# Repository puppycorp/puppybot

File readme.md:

# PuppyBot

PuppyBot's controller, Linux runtime, simulator, visual-control training and
classic ESP32 serial firmware are implemented in Flexscript. The maintained
source is in [`src/`](src/README.md), organized by purpose.

## Run

From the repository root:

```sh
flexscript run puppybot.flex
```

Open **http://127.0.0.1:8081/** for the robot dashboard. The default is a fake
servo bus. The launcher compiles and executes the native runtime; configuration
comes from [`puppybot.json`](puppybot.json). See the
[controller instructions](src/README.md) for physical serial control and output enable.

Run a separate 3D simulator with `flexscript run simulator.flex`. It prints the
private serial device and the controller connection command. For the lightweight
servo model use `flexscript run simulator.flex --servo-only`.

For autonomous simulation and visual-control experiments:

```sh
flexscript run sim.flex --list-cases
flexscript run sim.flex --case house-blocks-into-box --drift 10
./src/control.sh build
```

See [simulation](src/sim/README.md), [visual control](src/control/README.md),
[Gym](src/gym/README.md) and [exploration](src/exploration/README.md).
Python remains in experiment orchestration, data preparation and independent
verification; the repository is not exclusively Flexscript.

## Build and verify

Install Flexscript and keep the sibling `../flexscript` Git checkout available.
The native build snapshots a pinned compiler/library revision from that checkout
into `build/native-toolchain`; it never changes the sibling checkout. Set
`FLEXSCRIPT_SOURCE` to use another checkout containing that revision. To supply
an already verified matching toolchain instead, set `FLEXSCRIPT_COMPILER` and
`FLEXSCRIPT_ROOT` (and `FLEXSCRIPT_SOURCE` for firmware link tooling).

```sh
./src/scripts/build-runtime.sh
./src/scripts/test-runtime.sh
```

These commands build and test the native controller, HTTP/WebSocket runtime,
CLI, serial simulator and simulated firmware without the GPU training toolchain.
The tests use loopback sockets and private PTYs, not a physical robot.

The broader `./src/scripts/build.sh` and `./src/scripts/test.sh` include Gym,
vision, controller differential tests and additional tooling. They require a
compatible Flexscript source checkout and GPU libraries; set `FLEXSCRIPT_ROOT`
and follow [the detailed build instructions](src/README.md).

For classic ESP32 serial firmware:

```sh
python3 src/scripts/prepare-esp32-tools.py
./src/scripts/build-esp32.sh
```

See [firmware wiring, verification and flashing](src/firmware/README.md).
The Flexscript target is serial-only: Wi-Fi/WebSocket/mDNS, Android wireless
control, persistent calibration and physical hardware qualification are still
separate work. Replacing the source layout does not establish those capabilities.

## Repository layout

| Path | Purpose |
| --- | --- |
| `src/core/`, `src/transport/` | Shared controller, kinematics, safety and protocol |
| `src/runtime/`, `src/host/`, `src/cli/` | Linux service, dashboard, serial adapter and CLI |
| `src/firmware/`, `src/platform/` | ESP32 and simulated firmware adapters |
| `src/sim/`, `src/simulator/`, `src/gym/` | 3D simulation, serial plant and rollout UI |
| `src/control/`, `src/ml/`, `src/vision/`, `src/exploration/` | Learning, inference and navigation |
| `src/scripts/`, `src/tests/` | Build tools and verification |
| `tests/reference/rust-core/` | Original Rust controller used only as a test oracle |
| `datasets/`, `experiments/`, `diary/` | Dataset recipes, experiment programs and research notes |
| `build/flex/sim/` | Local generated datasets and experiment artifacts |
| `models/`, `robotdreams/` | Owned assets and retained historical scene/calibration evidence |
| `android/`, `python/`, `design/` | Android client, servo service utilities and electronics |

The Rust runtime, CLI, ESP32 firmware and collision tools are retired from the
maintained source tree; earlier versions remain in Git history. The native
build workflow packages Flexscript runtime binaries and the Flexscript ESP32
ROM image. The Android client remains a separate application.

`flex` is a compatibility symlink to `src`; `puppybot/core` points to the Rust
test reference. New development uses the canonical paths. Existing experiments,
receipts and `build/flex` output paths are not renamed by this migration.
Source changes still require fresh provenance checks before an old run can be
repeated; a compatibility path does not guarantee identical source hashes.

## Dataset storage

Actual data lives primarily under `build/flex/sim/`; `datasets/` contains recipes
and documentation. Follow [the storage rules](AGENTS.md#experiment-storage):
budget every run, preserve required evidence, review retention when it finishes,
and verify physical space recovered after cleanup. Git-ignored data is not
necessarily disposable.

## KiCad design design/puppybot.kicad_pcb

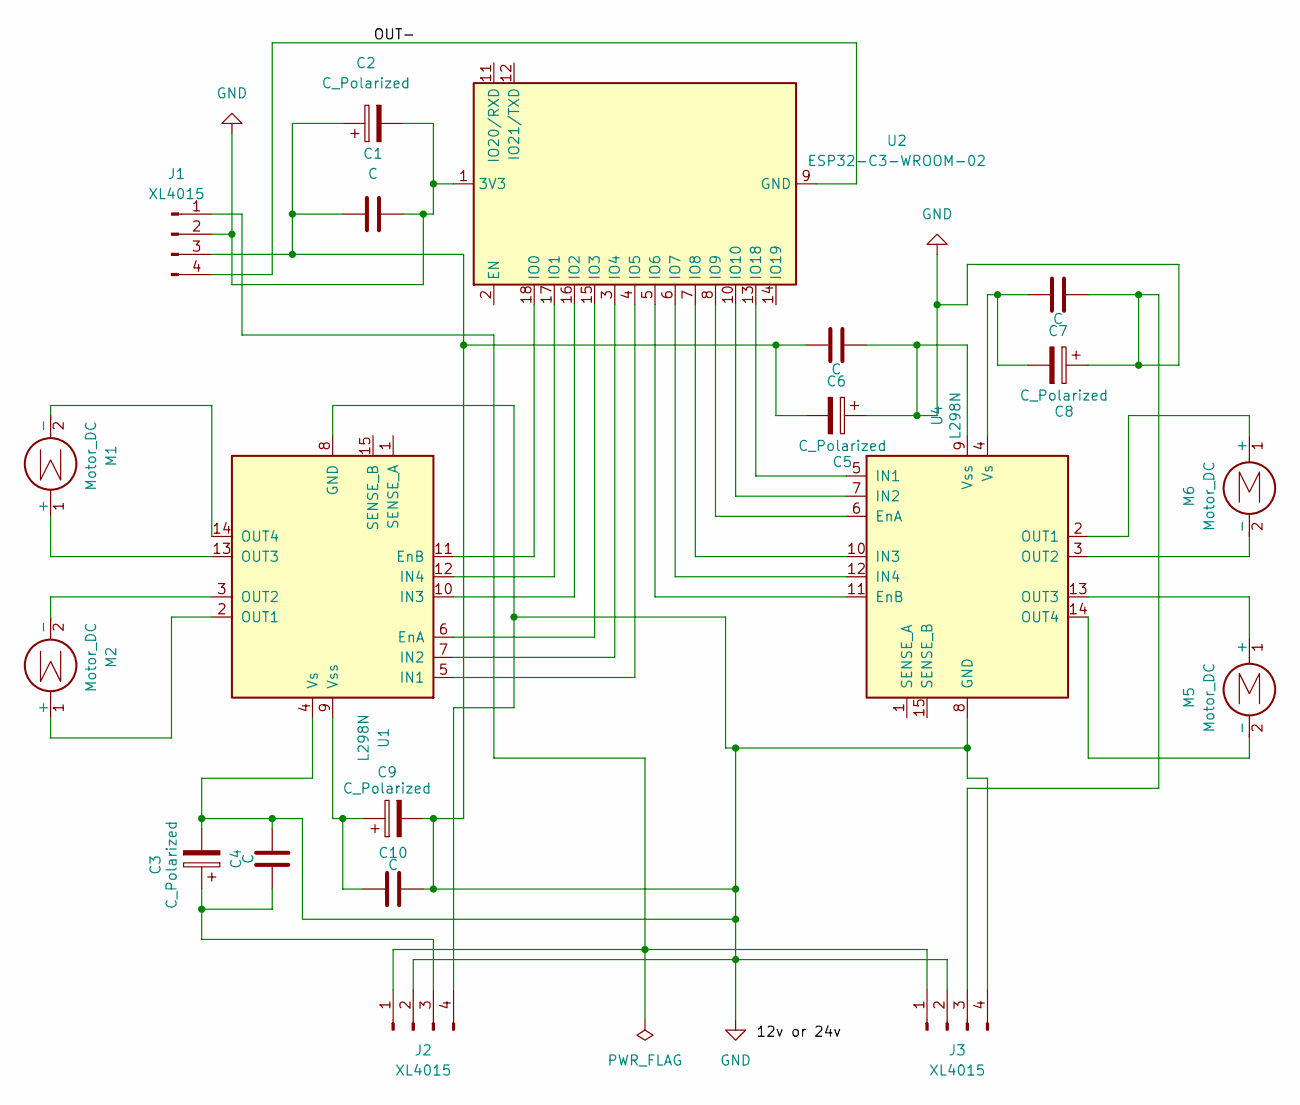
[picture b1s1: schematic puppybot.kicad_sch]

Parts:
C1, C4, C6, C7, C10: C; C_0805_2012Metric
C2, C3, C5, C8, C9: C_Polarized; CP_Radial_D5.0mm_P2.00mm
J1, J2, J3: XL4015; FanPinHeader_1x04_P2.54mm_Vertical
M1, M2, M5, M6: Motor_DC; TerminalBlock_RND_205-00234_1x04_P5.08mm_Horizontal
U1, U4: L298N; DIP-16_W7.62mm
U2: ESP32-C3-WROOM-02

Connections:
/OUT-: J1.4, U2.9 (GND), U2.19 (GND)
GND: C1.1, C1.2, C2.1, C2.2, C3.2, C4.2, C5.1, C5.2, C6.1, C6.2, C7.1, C8.1, C9.2, C10.2, J1.2, J1.3, J2.2, J2.4, J3.2, J3.3, J3.4, U1.4 (Vs), U1.8 (GND), U2.1 (3V3), U4.8 (GND), U4.9 (Vss)
unnamed: J1.1, J2.1, J3.1
unnamed: C3.1, C4.1, J2.3
unnamed: M1.1 (+), U1.13 (OUT3)
unnamed: M1.2 (-), U1.14 (OUT4)
unnamed: M2.1 (+), U1.2 (OUT1)
unnamed: M2.2 (-), U1.3 (OUT2)
unnamed: M5.1 (+), U4.13 (OUT3)
unnamed: M5.2 (-), U4.14 (OUT4)
unnamed: M6.1 (+), U4.2 (OUT1)
unnamed: M6.2 (-), U4.3 (OUT2)
unnamed: U1.6 (EnA), U2.15 (IO3)
unnamed: U1.11 (EnB), U2.18 (IO0)
unnamed: U1.5 (IN1), U2.4 (IO5)
unnamed: U1.7 (IN2), U2.3 (IO4)
unnamed: U1.10 (IN3), U2.16 (IO2)
unnamed: U1.12 (IN4), U2.17 (IO1)
unnamed: C9.1, C10.1, U1.9 (Vss)
unnamed: U2.5 (IO6), U4.11 (EnB)
unnamed: U2.6 (IO7), U4.12 (IN4)
unnamed: U2.7 (IO8), U4.10 (IN3)
unnamed: U2.8 (IO9), U4.6 (EnA)
unnamed: U2.10 (IO10), U4.7 (IN2)
unnamed: U2.13 (IO18), U4.5 (IN1)
unnamed: C7.2, C8.2, U4.4 (Vs)

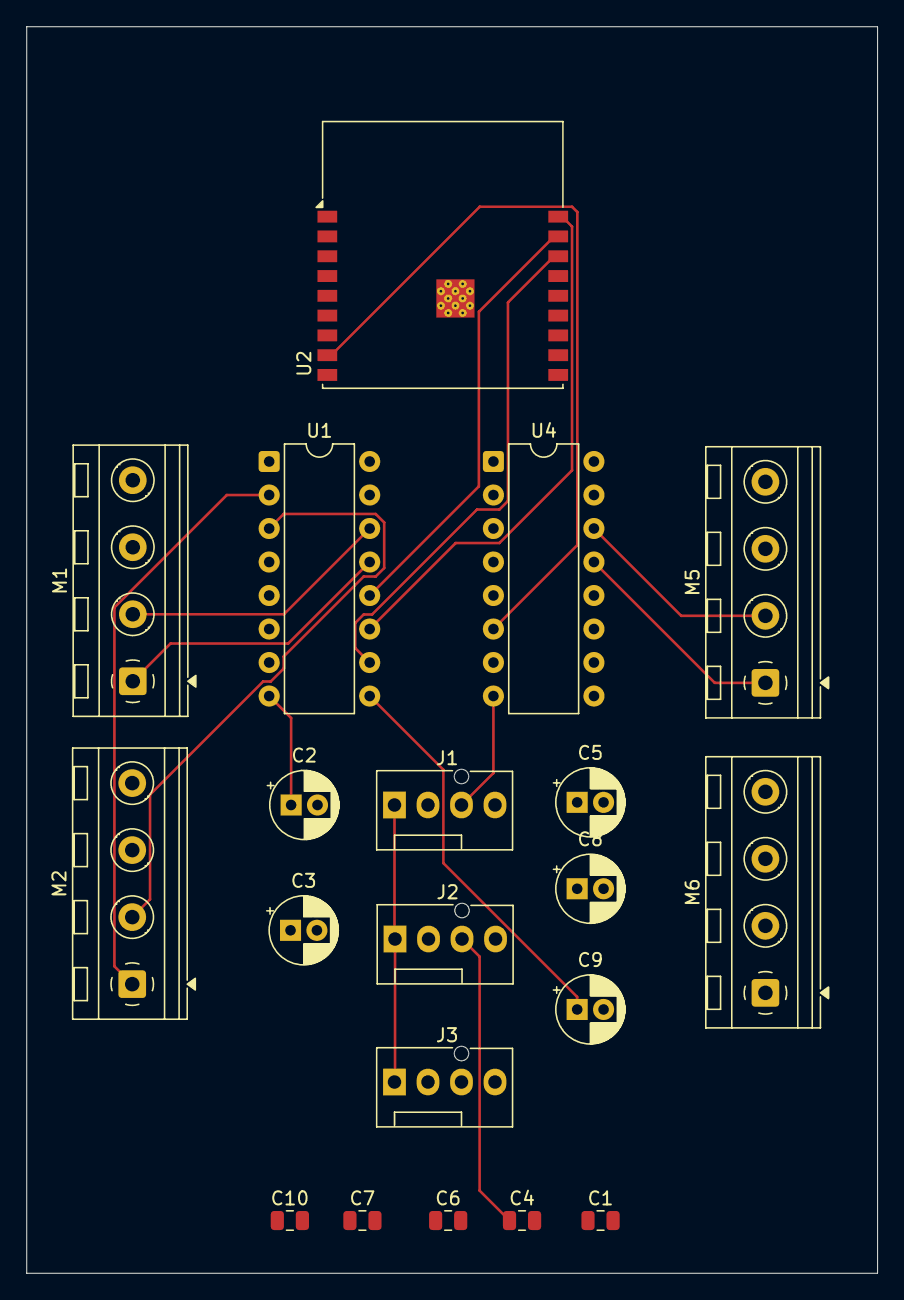
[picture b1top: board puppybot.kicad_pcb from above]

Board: 2 copper layers, 64.5 x 94.5 mm, 20 parts (0 on the bottom side), 26 nets.

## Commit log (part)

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2025-03-09 this is the way
2025-03-09 things
2025-03-22 update elecric design
2025-03-31 new things
2025-04-01 add things
2025-04-02 making structure
2025-04-07 add readme
2025-04-07 save
2025-04-07 start protocol impl
2025-04-09 code
2025-04-12 ping pong with esp works
2025-04-12 moving files and drive
2025-04-12 wow driving forward works
2025-04-13 improve controls now can move forward and backwards
2025-04-13 implement safety stopping of motors if command is not repeated
2025-04-17 trying to make bluetooth to work
2025-04-17 changes to motor control
2025-04-17 add esp32 build
2025-04-17 remove one readme
2025-04-17 dont upload firmware yet
2025-04-17 modify pipeline
2025-04-17 make SERVER_HOST optional
2025-04-17 run gitlab ci always
2025-04-17 change working directory
2025-04-17 add cache to esp32 build
2025-04-17 now the build should work
2025-05-20 Add Android app skeleton
2025-06-11 design change
2025-06-12 run clang format
2025-06-12 some agent things
2025-06-14 Document servo steering
2025-06-14 clang format all c and h files
2025-06-14 format
2025-06-14 run prettier format
2025-06-14 add npm run format to format script
2025-06-14 disable esp build from pipeline fro now
2025-06-14 it works
2025-06-14 add prepare-agent.sh
2025-06-15 Add servo steering control (#2)
2025-06-15 formating
2025-07-06 puppybot v0.6
2025-09-14 it works i guess
2025-09-14 initialize android app
2025-10-05 implement controlling the bot with android app
2025-10-05 Add joystick control mode to Android app
2025-10-05 fix not working with new espidf also add speed parsing
2025-10-05 fix build issues
2025-10-05 Add joystick control mode to Android app (#3)
2025-10-05 improve joystick controls
2025-10-06 adding bluetooth controlling support
2025-10-23 modify prepare agent to have bun install and android build
2025-10-23 ignore esp32/.cache/
2025-10-23 add start script to package.json
2025-10-23 add some development instructions into readme
2025-10-23 add deps and nodemodules to prettier ignore
2025-10-23 add dockerfile for testing agent preparation
2025-10-23 modify prepare_agent to setup the android environment propely
2025-10-23 implement test.sh script for running tests
2025-10-24 implementing puppyarm control things still bit todo
2025-10-24 shows puppybot variant and version in the ui
2025-10-24 modify agent instructions
2025-10-24 add wiring guid into readme
2025-10-24 Add pulse drive and servo controls to UI and protocol
    Adds pulse drive buttons and servo sliders to the UI. Updates the
    protocol to support pulse drive and servo angle commands. Implements
    support for these features in BLE, WebSocket, and ESP32 code.
2025-10-25 implement timeout for servo control
2025-10-25 improve prepare agent and agent instructions
2025-10-25 now we can define many wifi credentials
2025-10-25 start abstracting hardware
2025-10-25 Include platform-agnostic command_handler.c in build
2025-10-25 implement custom config format PuppyBotConfigLanguage
2025-10-25 add github actions build for android app
2025-10-25 run android build on every commit but only release when tagged
2025-10-25 change apk name to puppybot.apk
2025-10-25 skip cache if it is down
2025-10-25 wrong android release path
2025-10-25 trying to create autoupdate feature
2025-10-25 fix andrid build
2025-10-25 fix esp32 build
2025-10-25 Refactor CI workflows and add publish-release workflow
    - Rename and update Android and ESP32 build workflows
    - Add publish-release workflow to automate tagged releases
    - Standardize artifact packaging and outputs for reuse
2025-10-25 Rename artifact_path to artifact_file in workflows
2025-10-25 add support for parsing pbcl config but still very broken
2025-10-25 make ui nicer
2025-10-26 Rename server folder to fleet and update references
2025-10-26 Update server-build workflow to use fleet directory
2025-10-26 Add config templates for bots and support template selection in UI
2025-10-26 Add Zed task to start dev server with Bun
2025-10-26 Add motor control UI for angle and continuous motors
    Provides sliders and buttons for direct motor control in the bot
    configuration page, supporting both angle (servo) and
    continuous/h-bridge motors. Removes custom template marking logic for
    clarity.
2025-10-26 Refactor motor handling and add mDNS bot discovery
    - Replace hardcoded motor IDs with dynamic motor registry - Refactor
    servo timeout logic to use motor slots - Add mDNS-based bot discovery
    and auto-connect in fleet server - Move web client files to fleet/web
    and update imports - Remove unused server/types.ts file - Add
    command_handler_reload_motor_config for config reloads
2025-10-26 Prefer IPv4 address for mDNS host, add hostname field
2025-10-26 Remove legacy motorA/motorB control functions and wrappers
2025-10-26 Remove CMD_TURN_SERVO and handle servo turns via CMD_DRIVE_MOTOR
2025-10-26 Refactor platform abstraction and remove ops structs
2025-10-26 Remove unix_hardware.c source file
2025-10-27 Remove unnecessary extern "C" blocks from headers
2025-10-27 Move timing utilities to utility module and clean up motor API
2025-10-27 Update AGENTS.md with C code guidelines on extern "C" usage
2025-10-30 Refactor main app and motor config; add HTTP/WebSocket
    - Rename puppy_app.c to main.c and refactor to use new HTTP/WebSocket
    API - Move motor config logic to motor_config.c and motor_config.h -
    Remove legacy command, comm, and WebSocket files - Add src/http.c and
    src/http.h for platform-agnostic HTTP/WebSocket - Update ESP32 platform
    code to use new abstractions - Update tests and build scripts for new
    structure - Add uWebSockets as a submodule
2025-10-30 Add host platform stubs for desktop build
    Add host implementations for HTTP/WebSocket, logging, motor hardware,
    platform, and timer modules. Add main.c entry point and run.sh helper
    script for building and running on desktop. Update CMakeLists.txt to
    exclude test sources and link pthreads.
2025-10-30 Improve logging and add log rate limiting for motor commands
    - Add command_type_to_string helper for readable logs - Log motor
    commands with details in http.c and http_host.c - Implement log rate
    limiting for repeated drive motor commands - Enhance motor_hw_stub.c to
    suppress redundant PWM/H-bridge logs - Fix timer_host.c to improve timer
    accuracy and cancellation handling - Comment out unused servo code in
    motor_runtime.c
2025-11-16 prevent searcing from deps folder
2025-11-16 dont setn channel config in hw ensure pwm since no gpio not known
2025-11-16 remove unnessary calls
2025-11-16 init motor hw
2025-11-16 Fix WebSocket masking errors by using single-call receive pattern
    Changed ws_httpd_handler to use a static buffer with a single
    httpd_ws_recv_frame() call instead of the two-step pattern (first
    call with max_len=0, then with actual length).
    The two-step pattern triggers a known ESP-IDF bug where frames are
    incorrectly reported as "not properly masked" even when they are
    correctly masked according to RFC 6455.
2025-11-16 log parsed commands and if type is not regonized
2025-11-16 fixed some issues with command serialization now drive motor works
2025-11-23 fix rover turning not working in bot.ts
2025-12-12 restructure project files
2025-12-12 restructure project files more
2025-12-13 control and read serial servo state
2025-12-13 scan nodes from serial bus
2025-12-14 rename and format some fils
2025-12-14 modify web layout and servo status polling enabled option
2025-12-14 server create id for bot and store it
2025-12-14 more generic name
2025-12-22 angle control disabled by default
2025-12-22 add proper conversions for degrees
2025-12-22 dont move servos when config is applied
2025-12-22 store device config on disk and parse it when device connects
2025-12-22 use /api/bot/ws api path and always send motor config to server
2025-12-22 prevent mode switch and motor going crazy
2025-12-23 implement limit controls, improve bot layout and rename envs
2026-05-02 implement puppyarm controller
2026-05-02 implement missing things to the interface
2026-05-03 Rename fleet to mothership and update web UI design
2026-05-30 Harden BLE Permissions and Update Checks
2026-05-30 Link libm and guard protocol tests
2026-05-30 initialize rust version of puppybot firmware
2026-05-30 wifi support
2026-05-30 mdns discovery and websockets work
2026-05-30 Add servo config and drive commands
2026-05-30 add python scripts
2026-06-01 Add arm telemetry and subscription support
2026-06-01 jogging works
2026-06-01 Ignore Stale WebSocket Callbacks
2026-06-01 Add ST servo mock bus and ESP32 UART impl
2026-06-03 Add host simulator and shared protocol layer
2026-06-04 Refactor puppyarm worker
2026-06-04 Split puppybot Rust crates
2026-06-06 Rename host runtime and centralize protocol
2026-06-09 refactoring
2026-06-09 servobus runtime impl
2026-06-12 refactoring firmware
2026-06-12 Make runtime the default Rust target
2026-06-12 Refactor puppyarm module
2026-06-14 Refactor puppy arm safety API
2026-06-18 add missing safety tests doc
2026-06-18 Add PuppyArm goto retargeting test
2026-06-18 Add PuppyArm wrapped limit goto test
2026-06-18 Add PuppyArm wrap boundary jitter test
2026-06-18 Add PuppyArm free spin read failure test
2026-06-18 Add PuppyArm target tracking deadman test
2026-06-19 Add PuppyArm overtemperature safety test
2026-06-19 Add PuppyArm stall safety test
2026-06-19 disable server build
2026-06-19 add clear faults test
2026-06-19 Add PuppyArm target tracking regression tests
2026-06-19 Add PuppyArm calibration reference tests
2026-06-26 Add servo-device CLI override
2026-06-29 add runtime ui and control cli
2026-06-29 Fix PuppyArm yaw jog mapping
